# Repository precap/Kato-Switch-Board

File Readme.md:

The board is designed to throw single solenoid switches (e.g. Kato N-scale switches), and serve as multipurpose Expansion to a DCC-EX setup.

# Software
to be written. Help welcome.

# Hardware
Created in KiCad 6.10. Supposedly all the symbol libraries are included in KiCad 6 Projects. I have never tested that though, so let me know if there are any problems with loading.

## Arduino Nano Every
The Board is designed to run with an Arduino Nano Every exclusively (Note: Arduino Nano Every is distinct from Arduino Nano).
This is a conscious Design Decision, as the Nano Every has all the power supply components on board to generate sufficient 3.3V and 5V amperage to power the entire board from the higher Voltage input over the Barrel Jack.
Warning: Do not attempt to run Arduino Nano or other pin compatible boards that cannot handle high voltage on the VIN pin.

## Power Supply
should be provided to the 2.1mm Barrel Jack, or to the pins beside it marked 12V. Voltage fed here will go directly to the switches, LEDs, and to the VIN pin in the Arduino Nano Footprint.
The Arduino Nano Every can provide 1A of 5V, and up to 0.5A of that can further be converted to 3.3V. Most of this capability will be unused and is made available on the marked 2x2 pin headers for external use.

## Board Features
### Switches
Support for 12 Switches. Switching is performed by PT5126A-H chips. Supposedly they can manage up to 2.8A (Kato Switch will draw 0.5A@12V, Double crossover 2A).
Connectors are standard 1x2 pins with 2.54mm spacing for now.

### LED
Up to 128 Output pins. Using SM16206S, which seem to be a knockoff of the (magnitudes more expensive) TLC59282DBQR.
The outermst pins on the connectors are power supply, the others connected to the outputs.

### I2C
A PCA9617ADPJ i2c repeater is fitted on the board, allowing the i2c bus to reach a greater area. The chip can also translate between different voltage levels on the i2c bus, jumpers to set the voltage are provided.

### DCC
DCC Input over an optocopler is possible.

### RFID
Up to four RC522 RFID Reader breakout boards can be connected. The pin arrangement matches commonly found breakout boards, allowing connection with a 8 pin cable.
Whether this feature is can be added to the software in a way that supports all 4 readers remains to be seen, as the RC522 must be polled continuously to detect passing RFID Tags.

## Evaluation Testing

All Evaluation Testing was only performed in a feature incomplete Prototype Version.

| Component     | Status |
|---------------|--------|
| Switch Drivers| OK     |
| LED Drivers   | tbd    |
| I2C Repeater  | OK     |
| DCC Circuitry | no hw  |
| RFID Reader   | OK     |

# Production
All SMD Components are available @ jlcpcb at time of release.
Production files can be found in `jlcbcb-production/`. Only the SMD-only assembly files are complete at time of release.
10 boards, assembled with SMD Coponents only, are around 125$ before shipping and taxes. Placing all the Pins will push this to 200$.

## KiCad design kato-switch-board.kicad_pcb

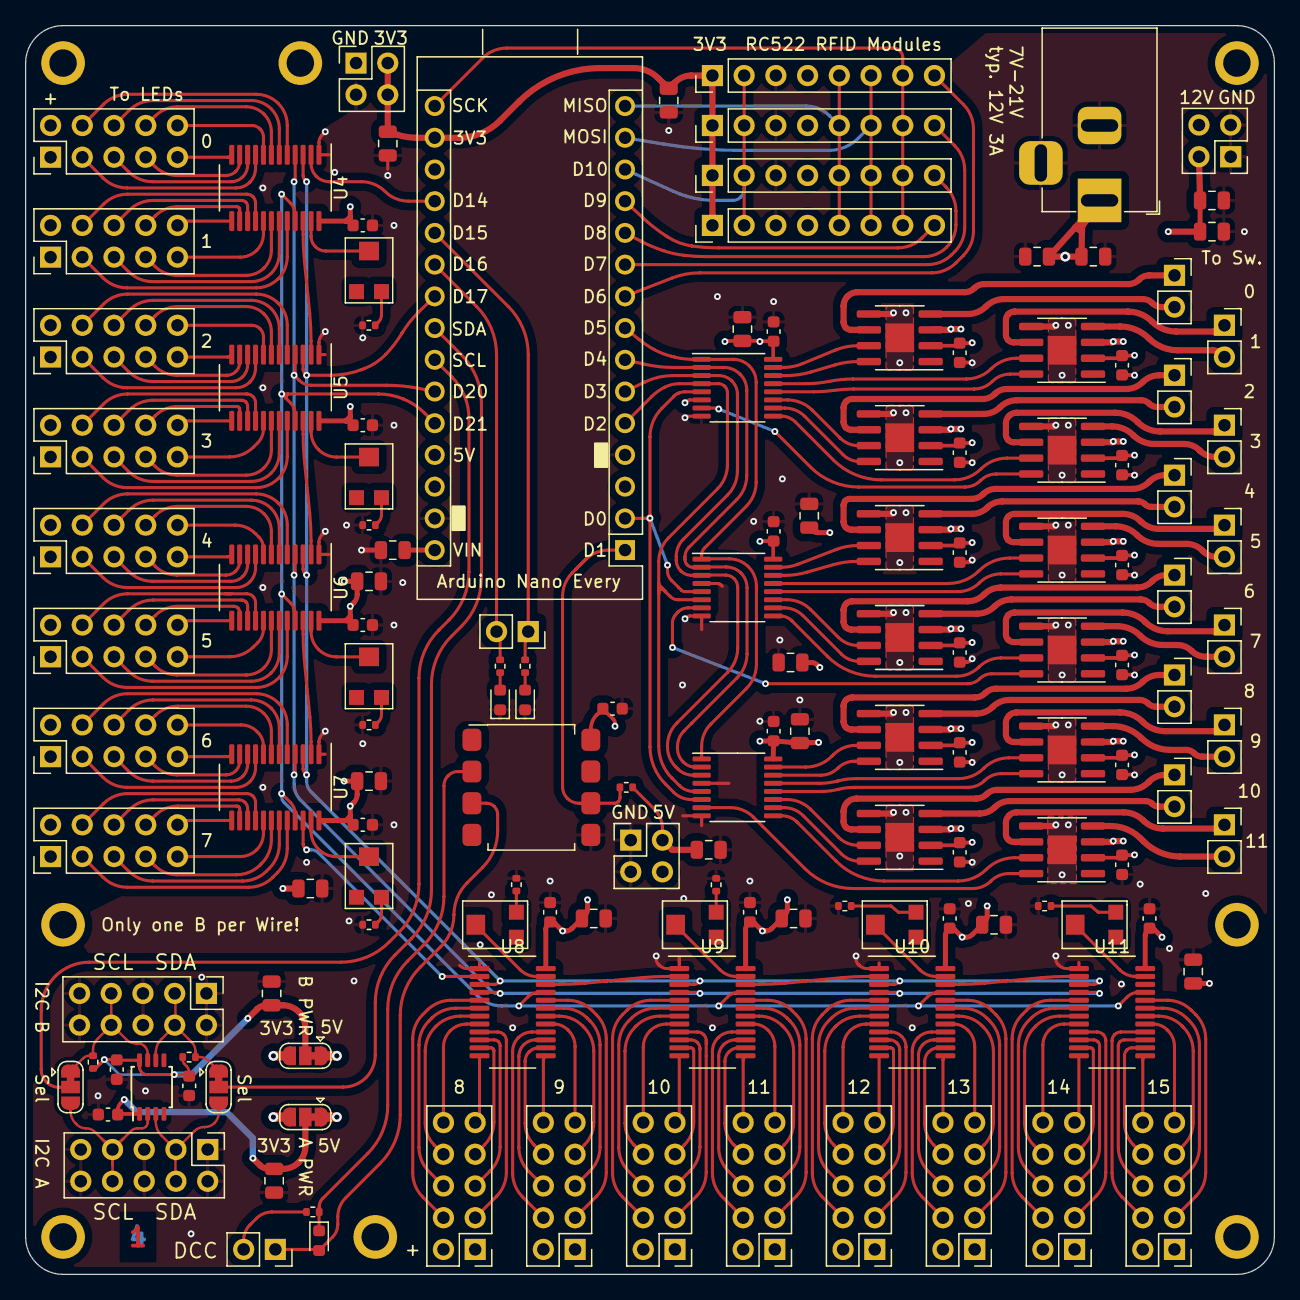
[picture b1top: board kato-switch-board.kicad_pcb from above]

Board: 4 copper layers, 100.0 x 100.0 mm, 151 parts (0 on the bottom side), 236 nets.

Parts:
A1: Arduino_Nano_Every; Arduino_Nano
C1, C2, C3, C4, C5, C6, C7, C8, C9, C31, C35: 22u; C_0805_2012Metric
C10, C11, C12, C13, C14, C15, C16, C17, C18, C19: 47u; C_0805_2012Metric
C20, C21, C22, C23, C24, C25, C26, C27, C28, C29, C30, C32, C33, C34, C36, C37, C38, C39, C40, C41, C42, C43, C44, C45, C46, C47, C48: 100nf; C_0603_1608Metric
D1, D2, D3: 0603_LED; LED_0603_1608Metric
H1, H2, H3, H4, H5, H6, H7, H8: MountingHole; MountingHole_2.2mm_M2_ISO7380_Pad
J1, J2, J3, J4: Conn_01x08; PinHeader_1x08_P2.54mm_Vertical
J5, J28, J29, J30, J31, J32, J33, J34, J35, J36, J37, J38, J39, J40: Conn_01x02; PinSocket_1x02_P2.54mm_Vertical
J6: Barrel_Jack_MountingPin; BarrelJack_Horizontal
J7, J8, J9: Conn_02x02_Odd_Even; PinHeader_2x02_P2.54mm_Vertical
J10, J11, J12, J13, J14, J15, J16, J17, J18, J19, J20, J21, J22, J23, J24, J25, J26, J27: Conn_02x05_Odd_Even; PinHeader_2x05_P2.54mm_Vertical
JP1, JP2, JP3, JP4: Jumper; SolderJumper-3_P1.3mm_Bridged12_RoundedPad1.0x1.5mm
R1, R2, R4, R6, R8, R10, R12, R14, R16, R18, R22: 2k2; R_0402_1005Metric
R3, R5, R7, R9, R11, R13, R15, R17: VG039NCHXTB503; VG039NCHXT
R19, R20, R21: 10k; R_0402_1005Metric
U1, U2, U3: 74HC238; TSSOP-16_4.4x5mm_P0.65mm
U4, U5, U6, U7, U8, U9, U10, U11: TLC59282DBQR...SM16206; QSOP-24_3.9x8.7mm_P0.635mm_rounded_pads
U12: PCA9617ADPJ; TSSOP-8_3x3mm_P0.65mm
U13, U14, U15, U16, U17, U18, U19, U20, U21, U22, U23, U24: PT5126A; HSOP-8-1EP_3.9x4.9mm_P1.27mm_EP2.3x2.3mm
U25: 6N137; SSO-8_6.7x9.8mm_P2.54mm_Clearance8mm

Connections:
+3V3: A1.17 (3V3), C10.1, C11.1, J1.1, J2.1, J3.1, J4.1, J9.2, J9.4, JP1.3 (B), JP2.3 (B)
+5V: A1.27 (+5V), C12.1, C13.1, C14.1, C15.1, C16.1, C17.1, C18.1, C19.1, C20.1, C21.1, C22.1, C23.2, C24.2, C25.2, C26.2, C27.2, C28.2, C29.2, C30.2, C36.1, C37.1, C38.1, C39.1, C40.1, C41.1, C42.1, C43.1, C44.1, C45.1, C46.1, C47.1, C48.1, J8.2, J8.4, JP1.1 (A), JP2.1 (A), R21.2, U1.6 (G1), U1.16 (VCC), U2.16 (VCC), U3.16 (VCC), U4.24 (VCC), U5.24 (VCC), U6.24 (VCC), U7.24 (VCC), U8.24 (VCC), U9.24 (VCC), U10.24 (VCC), U11.24 (VCC), U13.2 (VCC), U14.2 (VCC), U15.2 (VCC), U16.2 (VCC), U17.2 (VCC), U18.2 (VCC), U19.2 (VCC), U20.2 (VCC), U21.2 (VCC), U22.2 (VCC), U23.2 (VCC), U24.2 (VCC), U25.8 (VCC)
+12V: A1.30 (VIN), C1.1, C2.1, C3.1, C4.1, C5.1, C6.1, C7.1, C8.1, C9.1, J6.1, J7.2, J7.4, J10.1, J10.2, J11.1, J11.2, J12.1, J12.2, J13.1, J13.2, J14.1, J14.2, J15.1, J15.2, J16.1, J16.2, J17.1, J17.2, J18.1, J18.2, J19.1, J19.2, J20.1, J20.2, J21.1, J21.2, J22.1, J22.2, J23.1, J23.2, J24.1, J24.2, J25.1, J25.2, U13.3 (VM), U14.3 (VM), U15.3 (VM), U16.3 (VM), U17.3 (VM), U18.3 (VM), U19.3 (VM), U20.3 (VM), U21.3 (VM), U22.3 (VM), U23.3 (VM), U24.3 (VM)
/DCC_Input: A1.1 (TX1), R21.1, U25.6 (VO)
/DCC_signal/DCC_W1: J40.2, R22.2
/DCC_signal/DCC_W1_R: D3.1 (K), R22.1, U25.2 (A)
/DCC_signal/DCC_W2: D3.2 (A), J40.1, U25.3 (C)
/H-Bridge0/SWA: J28.2, U13.4 (OUTA)
/H-Bridge0/SWB: J28.1, U13.6 (OUTB)
/H-Bridge1/SWA: J29.2, U14.4 (OUTA)
/H-Bridge1/SWB: J29.1, U14.6 (OUTB)
/H-Bridge2/SWA: J30.2, U15.4 (OUTA)
/H-Bridge2/SWB: J30.1, U15.6 (OUTB)
/H-Bridge3/SWA: J31.2, U16.4 (OUTA)
/H-Bridge3/SWB: J31.1, U16.6 (OUTB)
/H-Bridge4/SWA: J32.2, U17.4 (OUTA)
/H-Bridge4/SWB: J32.1, U17.6 (OUTB)
/H-Bridge5/SWA: J33.2, U18.4 (OUTA)
/H-Bridge5/SWB: J33.1, U18.6 (OUTB)
/H-Bridge6/SWA: J34.2, U19.4 (OUTA)
/H-Bridge6/SWB: J34.1, U19.6 (OUTB)
/H-Bridge7/SWA: J35.2, U20.4 (OUTA)
/H-Bridge7/SWB: J35.1, U20.6 (OUTB)
/H-Bridge8/SWA: J36.2, U21.4 (OUTA)
/H-Bridge8/SWB: J36.1, U21.6 (OUTB)
/H-Bridge9/SWA: J37.2, U22.4 (OUTA)
/H-Bridge9/SWB: J37.1, U22.6 (OUTB)
/H-Bridge10/SWA: J38.2, U23.4 (OUTA)
/H-Bridge10/SWB: J38.1, U23.6 (OUTB)
/H-Bridge11/SWA: J39.2, U24.4 (OUTA)
/H-Bridge11/SWB: J39.1, U24.6 (OUTB)
/i2c_repeater/i2cA-vcc: C31.1, C32.1, JP1.2 (C), U12.1 (VCCA)
/i2c_repeater/i2cB-vcc: C33.1, C34.1, C35.1, JP2.2 (C), R19.2, R20.2, U12.8 (VCCB)
/i2c_repeater/scl_a: J27.7, J27.8, JP3.3 (B), U12.2 (SCLA)
/i2c_repeater/scl_b: J26.7, J26.8, JP3.1 (A), R19.1, U12.7 (SCLB)
/i2c_repeater/sda_a: J27.3, J27.4, JP4.3 (B), U12.3 (SDAA)
/i2c_repeater/sda_b: J26.3, J26.4, JP4.1 (A), R20.1, U12.6 (SDAB)
/ina0: U1.15 (Y0), U13.7 (INA)
/ina1: U1.13 (Y2), U14.7 (INA)
/ina2: U1.11 (Y4), U15.7 (INA)
/ina3: U1.9 (Y6), U16.7 (INA)
/ina4: U2.15 (Y0), U17.7 (INA)
/ina5: U2.13 (Y2), U18.7 (INA)
/ina6: U2.11 (Y4), U19.7 (INA)
/ina7: U2.9 (Y6), U20.7 (INA)
/ina8: U3.15 (Y0), U21.7 (INA)
/ina9: U3.13 (Y2), U22.7 (INA)
/ina10: U3.11 (Y4), U23.7 (INA)
/ina11: U3.9 (Y6), U24.7 (INA)
/inb0: U1.14 (Y1), U13.8 (INB)
/inb1: U1.12 (Y3), U14.8 (INB)
/inb2: U1.10 (Y5), U15.8 (INB)
/inb3: U1.7 (Y7), U16.8 (INB)
/inb4: U2.14 (Y1), U17.8 (INB)
/inb5: U2.12 (Y3), U18.8 (INB)
/inb6: U2.10 (Y5), U19.8 (INB)
/inb7: U2.7 (Y7), U20.8 (INB)
/inb8: U3.14 (Y1), U21.8 (INB)
/inb9: U3.12 (Y3), U22.8 (INB)
/inb10: U3.10 (Y5), U23.8 (INB)
/inb11: U3.7 (Y7), U24.8 (INB)
/latch_en: A1.25 (A6), U4.4 (Latch_en), U5.4 (Latch_en), U6.4 (Latch_en), U7.4 (Latch_en), U8.4 (Latch_en), U9.4 (Latch_en), U10.4 (Latch_en), U11.4 (Latch_en)
/leds0/iref: R3.2 (Wiper), U4.23 (IREF)
/leds0/led0: J10.4, U4.5 (Out0)
/leds0/led1: J10.6, U4.6 (Out1)
/leds0/led2: J10.8, U4.7 (Out2)
/leds0/led3: J10.10, U4.8 (Out3)
/leds0/led4: J10.3, U4.9 (Out4)
/leds0/led5: J10.5, U4.10 (Out5)
/leds0/led6: J10.7, U4.11 (Out6)
/leds0/led7: J10.9, U4.12 (Out7)
/leds0/led8: J11.10, U4.13 (Out8)
/leds0/led9: J11.8, U4.14 (Out9)
/leds0/led10: J11.6, U4.15 (Out10)
/leds0/led11: J11.4, U4.16 (Out11)
/leds0/led12: J11.9, U4.17 (Out12)
/leds0/led13: J11.7, U4.18 (Out13)
/leds0/led14: J11.5, U4.19 (Out14)
/leds0/led15: J11.3, U4.20 (Out15)
/leds0/pot: R3.1 (A), R4.1
/leds1/iref: R5.2 (Wiper), U5.23 (IREF)
/leds1/led0: J12.4, U5.5 (Out0)
/leds1/led1: J12.6, U5.6 (Out1)
/leds1/led2: J12.8, U5.7 (Out2)
/leds1/led3: J12.10, U5.8 (Out3)
/leds1/led4: J12.3, U5.9 (Out4)
/leds1/led5: J12.5, U5.10 (Out5)
/leds1/led6: J12.7, U5.11 (Out6)
/leds1/led7: J12.9, U5.12 (Out7)
/leds1/led8: J13.10, U5.13 (Out8)
/leds1/led9: J13.8, U5.14 (Out9)
/leds1/led10: J13.6, U5.15 (Out10)
/leds1/led11: J13.4, U5.16 (Out11)
/leds1/led12: J13.9, U5.17 (Out12)
/leds1/led13: J13.7, U5.18 (Out13)
/leds1/led14: J13.5, U5.19 (Out14)
/leds1/led15: J13.3, U5.20 (Out15)
/leds1/pot: R5.1 (A), R6.1
/leds2/iref: R7.2 (Wiper), U6.23 (IREF)
/leds2/led0: J14.4, U6.5 (Out0)
/leds2/led1: J14.6, U6.6 (Out1)
/leds2/led2: J14.8, U6.7 (Out2)
/leds2/led3: J14.10, U6.8 (Out3)
/leds2/led4: J14.3, U6.9 (Out4)
/leds2/led5: J14.5, U6.10 (Out5)
/leds2/led6: J14.7, U6.11 (Out6)
/leds2/led7: J14.9, U6.12 (Out7)
/leds2/led8: J15.10, U6.13 (Out8)
/leds2/led9: J15.8, U6.14 (Out9)
/leds2/led10: J15.6, U6.15 (Out10)
/leds2/led11: J15.4, U6.16 (Out11)
/leds2/led12: J15.9, U6.17 (Out12)
/leds2/led13: J15.7, U6.18 (Out13)
/leds2/led14: J15.5, U6.19 (Out14)
/leds2/led15: J15.3, U6.20 (Out15)
/leds2/pot: R7.1 (A), R8.1
/leds3/iref: R9.2 (Wiper), U7.23 (IREF)
/leds3/led0: J16.4, U7.5 (Out0)
/leds3/led1: J16.6, U7.6 (Out1)
/leds3/led2: J16.8, U7.7 (Out2)
/leds3/led3: J16.10, U7.8 (Out3)
/leds3/led4: J16.3, U7.9 (Out4)
/leds3/led5: J16.5, U7.10 (Out5)
/leds3/led6: J16.7, U7.11 (Out6)
/leds3/led7: J16.9, U7.12 (Out7)
/leds3/led8: J17.10, U7.13 (Out8)
/leds3/led9: J17.8, U7.14 (Out9)
/leds3/led10: J17.6, U7.15 (Out10)
/leds3/led11: J17.4, U7.16 (Out11)
/leds3/led12: J17.9, U7.17 (Out12)
/leds3/led13: J17.7, U7.18 (Out13)
/leds3/led14: J17.5, U7.19 (Out14)
/leds3/led15: J17.3, U7.20 (Out15)
/leds3/pot: R9.1 (A), R10.1
/leds4/iref: R11.2 (Wiper), U8.23 (IREF)
/leds4/led0: J18.4, U8.5 (Out0)
/leds4/led1: J18.6, U8.6 (Out1)
/leds4/led2: J18.8, U8.7 (Out2)
/leds4/led3: J18.10, U8.8 (Out3)
/leds4/led4: J18.3, U8.9 (Out4)
/leds4/led5: J18.5, U8.10 (Out5)
/leds4/led6: J18.7, U8.11 (Out6)
/leds4/led7: J18.9, U8.12 (Out7)
/leds4/led8: J19.10, U8.13 (Out8)
/leds4/led9: J19.8, U8.14 (Out9)
/leds4/led10: J19.6, U8.15 (Out10)
/leds4/led11: J19.4, U8.16 (Out11)
/leds4/led12: J19.9, U8.17 (Out12)
/leds4/led13: J19.7, U8.18 (Out13)
/leds4/led14: J19.5, U8.19 (Out14)
/leds4/led15: J19.3, U8.20 (Out15)
/leds4/pot: R11.1 (A), R12.1
/leds5/iref: R13.2 (Wiper), U9.23 (IREF)
/leds5/led0: J20.4, U9.5 (Out0)
/leds5/led1: J20.6, U9.6 (Out1)
/leds5/led2: J20.8, U9.7 (Out2)
/leds5/led3: J20.10, U9.8 (Out3)
/leds5/led4: J20.3, U9.9 (Out4)
/leds5/led5: J20.5, U9.10 (Out5)
/leds5/led6: J20.7, U9.11 (Out6)
/leds5/led7: J20.9, U9.12 (Out7)
/leds5/led8: J21.10, U9.13 (Out8)
/leds5/led9: J21.8, U9.14 (Out9)
/leds5/led10: J21.6, U9.15 (Out10)
/leds5/led11: J21.4, U9.16 (Out11)
/leds5/led12: J21.9, U9.17 (Out12)
/leds5/led13: J21.7, U9.18 (Out13)
/leds5/led14: J21.5, U9.19 (Out14)
/leds5/led15: J21.3, U9.20 (Out15)
/leds5/pot: R13.1 (A), R14.1
/leds6/iref: R15.2 (Wiper), U10.23 (IREF)
/leds6/led0: J22.4, U10.5 (Out0)
/leds6/led1: J22.6, U10.6 (Out1)
/leds6/led2: J22.8, U10.7 (Out2)
/leds6/led3: J22.10, U10.8 (Out3)
/leds6/led4: J22.3, U10.9 (Out4)
/leds6/led5: J22.5, U10.10 (Out5)
/leds6/led6: J22.7, U10.11 (Out6)
/leds6/led7: J22.9, U10.12 (Out7)
/leds6/led8: J23.10, U10.13 (Out8)
/leds6/led9: J23.8, U10.14 (Out9)
/leds6/led10: J23.6, U10.15 (Out10)
/leds6/led11: J23.4, U10.16 (Out11)
/leds6/led12: J23.9, U10.17 (Out12)
/leds6/led13: J23.7, U10.18 (Out13)
/leds6/led14: J23.5, U10.19 (Out14)
/leds6/led15: J23.3, U10.20 (Out15)
/leds6/pot: R15.1 (A), R16.1
/leds7/iref: R17.2 (Wiper), U11.23 (IREF)
/leds7/led0: J24.4, U11.5 (Out0)
/leds7/led1: J24.6, U11.6 (Out1)
/leds7/led2: J24.8, U11.7 (Out2)
/leds7/led3: J24.10, U11.8 (Out3)
/leds7/led4: J24.3, U11.9 (Out4)
/leds7/led5: J24.5, U11.10 (Out5)
/leds7/led6: J24.7, U11.11 (Out6)
/leds7/led7: J24.9, U11.12 (Out7)
/leds7/led8: J25.10, U11.13 (Out8)
/leds7/led9: J25.8, U11.14 (Out9)
/leds7/led10: J25.6, U11.15 (Out10)
/leds7/led11: J25.4, U11.16 (Out11)
/leds7/led12: J25.9, U11.17 (Out12)
/leds7/led13: J25.7, U11.18 (Out13)
/leds7/led14: J25.5, U11.19 (Out14)
/leds7/led15: J25.3, U11.20 (Out15)
/leds7/pot: R17.1 (A), R18.1
/oe_n: A1.26 (A7), U4.21 (oe_n), U5.21 (oe_n), U6.21 (oe_n), U7.21 (oe_n), U8.21 (oe_n), U9.21 (oe_n), U10.21 (oe_n), U11.21 (oe_n)
/scl: A1.24 (SCL/A5), JP3.2 (C)
/sda: A1.23 (SDA/A4), JP4.2 (C)
/sel0: A1.8 (D5), U1.1 (A0), U2.1 (A0), U3.1 (A0)
/sel1: A1.7 (D4), U1.2 (A1), U2.2 (A1), U3.2 (A1)
/sel2: A1.6 (D3), U1.3 (A2), U2.3 (A2), U3.3 (A2)
/sel3: A1.5 (D2), U1.4 (~G2A), U2.6 (G1), U3.5 (~G2B)
/sel4: A1.2 (RX1), U1.5 (~G2B), U2.5 (~G2B), U3.6 (G1)
/shift0: A1.19 (A0), U4.2 (SDI)
/shift1: U4.22 (SDO), U5.2 (SDI)
/shift2: U5.22 (SDO), U6.2 (SDI)
/shift3: U6.22 (SDO), U7.2 (SDI)
/shift4: U7.22 (SDO), U8.2 (SDI)
/shift5: U8.22 (SDO), U9.2 (SDI)
/shift6: U9.22 (SDO), U10.2 (SDI)
/shift7: U10.22 (SDO), U11.2 (SDI)
/shiftclk: A1.22 (A3), U4.3 (sclk), U5.3 (sclk), U6.3 (sclk), U7.3 (sclk), U8.3 (sclk), U9.3 (sclk), U10.3 (sclk), U11.3 (sclk)
/user_led: A1.20 (A1), J5.1, R1.2
/user_led2: A1.21 (A2), J5.2, R2.2
D11 / MOSI: A1.14 (MOSI), J1.6, J2.6, J3.6, J4.6
D12 / MISO: A1.15 (MISO), J1.5, J2.5, J3.5, J4.5
D13 / SCLK: A1.16 (SCK), J1.7, J2.7, J3.7, J4.7
GND: A1.4 (GND), A1.29 (GND), C1.2, C2.2, C3.2, C4.2, C5.2, C6.2, C7.2, C8.2, C9.2, C10.2, C11.2, C12.2, C13.2, C14.2, C15.2, C16.2, C17.2, C18.2, C19.2, C20.2, C21.2, C22.2, C23.1, C24.1, C25.1, C26.1, C27.1, C28.1, C29.1, C30.1, C31.2, C32.2, C33.2, C34.2, C35.2, C36.2, C37.2, C38.2, C39.2, C40.2, C41.2, C42.2, C43.2, C44.2, C45.2, C46.2, C47.2, C48.2, D1.1 (K), D2.1 (K), J1.3, J2.3, J3.3, J4.3, J6.2, J6.MP (MountPin), J7.1, J7.3, J8.1, J8.3, J9.1, J9.3, J26.1, J26.2, J26.5, J26.6, J26.9, J26.10, J27.1, J27.2, J27.5, J27.6, J27.9, J27.10, R4.2, R6.2, R8.2, R10.2, R12.2, R14.2, R16.2, R18.2, U1.8 (GND), U2.4 (~G2A), U2.8 (GND), U3.4 (~G2A), U3.8 (GND), U4.1 (GND), U5.1 (GND), U6.1 (GND), U7.1 (GND), U8.1 (GND), U9.1 (GND), U10.1 (GND), U11.1 (GND), U12.4 (GND), U13.5 (GND), U13.9 (PGND), U14.5 (GND), U14.9 (PGND), U15.5 (GND), U15.9 (PGND), U16.5 (GND), U16.9 (PGND), U17.5 (GND), U17.9 (PGND), U18.5 (GND), U18.9 (PGND), U19.5 (GND), U19.9 (PGND), U20.5 (GND), U20.9 (PGND), U21.5 (GND), U21.9 (PGND), U22.5 (GND), U22.9 (PGND), U23.5 (GND), U23.9 (PGND), U24.5 (GND), U24.9 (PGND), U25.5 (GND)
unnamed: D1.2 (A), R1.1
unnamed: D2.2 (A), R2.1
RFID_1_CS: A1.9 (D6), J1.8
RFID_2_CS: A1.10 (D7), J2.8
RFID_3_CS: A1.11 (D8), J3.8
RFID_4_CS: A1.12 (D9), J4.8
RFID_RESET: A1.13 (D10), J1.2, J2.2, J3.2, J4.2

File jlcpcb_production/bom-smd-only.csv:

Designator,Footprint,Comment,LCSC Part Number
"C1, C2, C3, C31, C35, C4, C5, C6, C7, C8, C9",0805,22u,C45783 
"C10, C11, C12, C13, C14, C15, C16, C17, C18, C19",0805,47u,C16780 
"C20, C21, C22, C23, C24, C25, C26, C27, C28, C29, C30, C32, C33, C34, C36, C37, C38, C39, C40, C41, C42, C43, C44, C45, C46, C47, C48",0603,100nf,C14663 
"D1, D2, D3",0603,0603_LED,C72043 
"R1, R10, R12, R14, R16, R18, R2, R22, R4, R6, R8",0402,2k2,C25879 
"R11, R13, R15, R17, R3, R5, R7, R9",SMD,VG039NCHXTB503,C145161 
"R19, R20, R21",0402,10k,C25744 
"U1, U2, U3",TSSOP-16,74HC238,C60434 
"U10, U11, U4, U5, U6, U7, U8, U9",QSOP-24,SM16206,C121618 
U12,TSSOP-8,PCA9617ADPJ,C128388 
"U13, U14, U15, U16, U17, U18, U19, U20, U21, U22, U23, U24",HSOP-8-1,PT5126A,C782185 
U25,SSO-8,6N137,C110020

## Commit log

2023-01-12 add image
2023-01-14 silkscreen & pad changes
2023-01-14 use only rounded pads
